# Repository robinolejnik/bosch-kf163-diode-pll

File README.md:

# bosch-kf163-diode-pll
PCB for programming the frequency of Bosch KF-mini-S radios (KF83, KF163, KF453, KFE165, KFE455) by soldering in diodes.

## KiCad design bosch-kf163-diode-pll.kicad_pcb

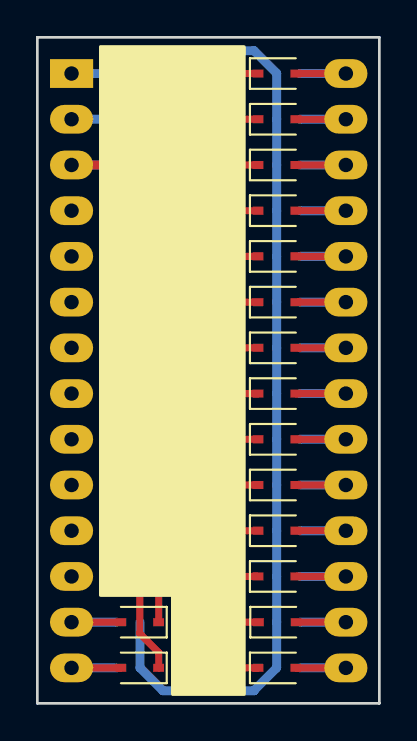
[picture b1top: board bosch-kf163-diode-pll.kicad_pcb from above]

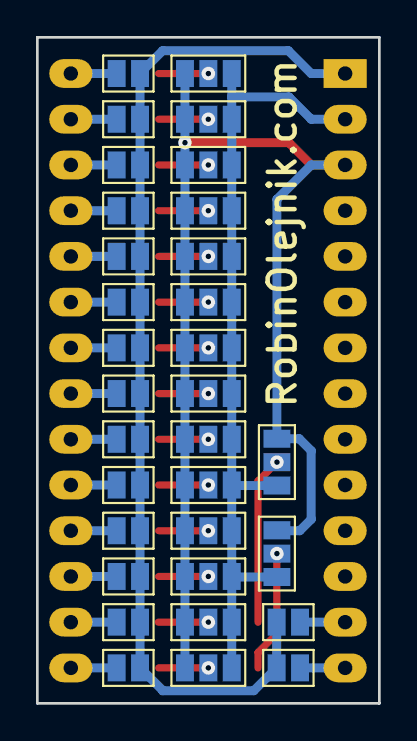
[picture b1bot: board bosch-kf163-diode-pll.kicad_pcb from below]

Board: 2 copper layers, 19.0 x 37.0 mm, 49 parts (32 on the bottom side), 35 nets.

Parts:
D1, D2, D3, D4, D5, D6, D7, D8, D9, D10, D11, D12, D13, D14, D15, D16: 1N4148W; D_SOD-323
JP1, JP2, JP3, JP4, JP5, JP6, JP7, JP8, JP9, JP10, JP11, JP12, JP13, JP14, JP15, JP16: SolderJumper_3_Open; SolderJumper-3_P1.3mm_Open_Pad1.0x1.5mm
JP17, JP18, JP19, JP20, JP21, JP22, JP23, JP24, JP25, JP26, JP27, JP28, JP29, JP30, JP31, JP32: SolderJumper_2_Open; SolderJumper-2_P1.3mm_Open_Pad1.0x1.5mm
U1: PLL; DIP-28_W15.24mm_LongPads

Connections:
GND: JP17.1 (A), JP18.1 (A), JP19.1 (A), JP20.1 (A), JP21.1 (A), JP22.1 (A), JP23.1 (A), JP24.1 (A), JP25.1 (A), JP26.1 (A), JP27.1 (A), JP28.1 (A), JP29.1 (A), JP30.1 (A), JP31.1 (A), JP32.1 (A), U1.1 (GND)
unnamed: D1.1 (K), JP1.2 (C)
unnamed: D1.2 (A), JP17.2 (B), U1.28 (STEPSIZE)
unnamed: D2.1 (K), JP2.2 (C)
unnamed: D2.2 (A), JP18.2 (B), U1.27 (A)
unnamed: D3.1 (K), JP3.2 (C)
unnamed: D3.2 (A), JP19.2 (B), U1.26 (B)
unnamed: D4.1 (K), JP4.2 (C)
unnamed: D4.2 (A), JP20.2 (B), U1.25 (C)
unnamed: D5.1 (K), JP5.2 (C)
unnamed: D5.2 (A), JP21.2 (B), U1.24 (D)
unnamed: D6.1 (K), JP6.2 (C)
unnamed: D6.2 (A), JP22.2 (B), U1.23 (E)
unnamed: D7.1 (K), JP7.2 (C)
unnamed: D7.2 (A), JP23.2 (B), U1.22 (F)
unnamed: D8.1 (K), JP8.2 (C)
unnamed: D8.2 (A), JP24.2 (B), U1.21 (G)
unnamed: D9.1 (K), JP9.2 (C)
unnamed: D9.2 (A), JP25.2 (B), U1.20 (H)
unnamed: D10.1 (K), JP10.2 (C)
unnamed: D10.2 (A), JP26.2 (B), U1.19 (64)
unnamed: D11.1 (K), JP11.2 (C)
unnamed: D11.2 (A), JP27.2 (B), U1.18 (32)
unnamed: D12.1 (K), JP12.2 (C)
unnamed: D12.2 (A), JP28.2 (B), U1.17 (16)
unnamed: D13.1 (K), JP13.2 (C)
unnamed: D13.2 (A), JP29.2 (B), U1.16 (8)
unnamed: D14.1 (K), JP14.2 (C)
unnamed: D14.2 (A), JP30.2 (B), U1.15 (4)
unnamed: D15.1 (K), JP15.2 (C)
unnamed: D15.2 (A), JP31.2 (B), U1.14 (2)
unnamed: D16.1 (K), JP16.2 (C)
unnamed: D16.2 (A), JP32.2 (B), U1.13 (1)
unnamed: JP1.1 (A), JP2.1 (A), JP3.1 (A), JP4.1 (A), JP5.1 (A), JP6.1 (A), JP7.1 (A), JP8.1 (A), JP9.1 (A), JP10.1 (A), JP11.1 (A), JP12.1 (A), JP13.1 (A), JP14.1 (A), JP15.1 (A), JP16.1 (A), U1.3 (AT)
unnamed: JP1.3 (B), JP2.3 (B), JP3.3 (B), JP4.3 (B), JP5.3 (B), JP6.3 (B), JP7.3 (B), JP8.3 (B), JP9.3 (B), JP10.3 (B), JP11.3 (B), JP12.3 (B), JP13.3 (B), JP14.3 (B), JP15.3 (B), JP16.3 (B), U1.2 (AR)

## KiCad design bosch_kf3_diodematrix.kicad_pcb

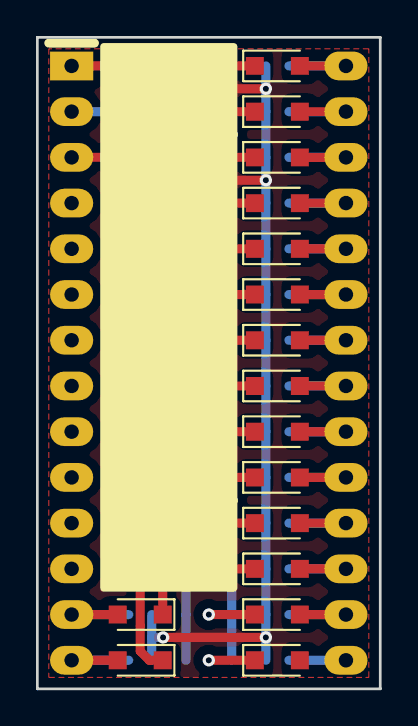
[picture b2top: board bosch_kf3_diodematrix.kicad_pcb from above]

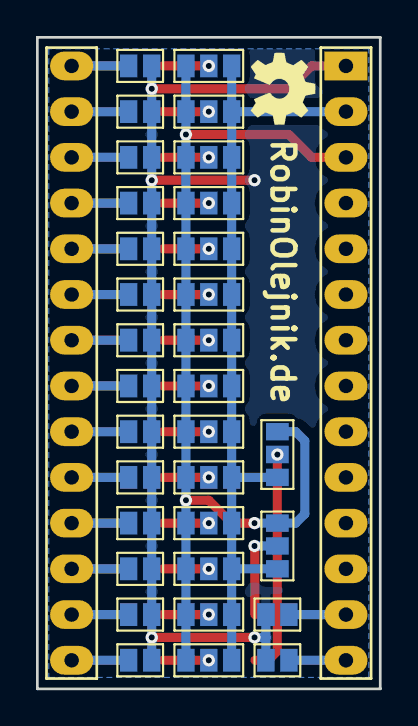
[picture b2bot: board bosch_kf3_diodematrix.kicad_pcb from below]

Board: 2 copper layers, 19.0 x 36.2 mm, 49 parts (32 on the bottom side), 35 nets.

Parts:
D1, D2, D3, D4, D5, D6, D7, D8, D9, D10, D11, D12, D13, D14, D15, D16: 1N4148; D_SOD-323_HandSoldering
J1, J2, J3, J4, J5, J6, J7, J8, J9, J10, J11, J12, J13, J14, J15, J16: GS3
J17, J18, J19, J20, J21, J22, J23, J24, J25, J26, J27, J28, J29, J30, J31, J32: GS2
U1: PLL; bosch_kf-mini-s_pll

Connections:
GND: J17.2, J18.2, J19.2, J20.2, J21.2, J22.2, J23.2, J24.2, J25.2, J26.2, J27.2, J28.2, J29.2, J30.2, J31.2, J32.2, U1.1
unnamed: D1.1, J1.2
unnamed: D1.2, J17.1, U1.28
unnamed: D2.1, J2.2
unnamed: D2.2, J18.1, U1.27
unnamed: D3.1, J3.2
unnamed: D3.2, J19.1, U1.26
unnamed: D4.1, J4.2
unnamed: D4.2, J20.1, U1.25
unnamed: D5.1, J5.2
unnamed: D5.2, J21.1, U1.24
unnamed: D6.1, J6.2
unnamed: D6.2, J22.1, U1.23
unnamed: D7.1, J7.2
unnamed: D7.2, J23.1, U1.22
unnamed: D8.1, J8.2
unnamed: D8.2, J24.1, U1.21
unnamed: D9.1, J9.2
unnamed: D9.2, J25.1, U1.20
unnamed: D10.1, J10.2
unnamed: D10.2, J26.1, U1.19
unnamed: D11.1, J11.2
unnamed: D11.2, J27.1, U1.18
unnamed: D12.1, J12.2
unnamed: D12.2, J28.1, U1.17
unnamed: D13.1, J13.2
unnamed: D13.2, J29.1, U1.16
unnamed: D14.1, J14.2
unnamed: D14.2, J30.1, U1.15
unnamed: D15.1, J15.2
unnamed: D15.2, J31.1, U1.14
unnamed: D16.1, J16.2
unnamed: D16.2, J32.1, U1.13
unnamed: J1.1, J2.1, J3.1, J4.1, J5.1, J6.1, J7.1, J8.1, J9.1, J10.1, J11.1, J12.1, J13.1, J14.1, J15.1, J16.1, U1.2
unnamed: J1.3, J2.3, J3.3, J4.3, J5.3, J6.3, J7.3, J8.3, J9.3, J10.3, J11.3, J12.3, J13.3, J14.3, J15.3, J16.3, U1.3

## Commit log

2017-09-26 Added kicad files
2019-01-22 Updated project to KiCad 5
2021-04-04 Schematic cleanup, proper symbol lib management and file renaming
2022-01-10 Complete remake with KiCad 6
2022-01-20 changed to smaller diodes, added schematic pdf and gerbers
2022-01-21 Added calculator.html
2022-01-23 calculator work in progress

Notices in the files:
bosch-kf163-diode-pll.kicad_pcb:
License: MIT
